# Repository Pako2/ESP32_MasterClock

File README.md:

# ESP32_MasterClock
## Introduction
The project addresses the solution of a simple source of polarized pulses for slave clock networks. The precise time is obtained from the internet using the NTP protocol. The heart of the device is the **ESP32-C3 SuperMini** module, which connects to the internet via WiFi. A prerequisite for the proper functioning of the device is, of course, an available WiFi signal at the deployment location.
The distribution of pulses is managed by a module equipped with two **A4950** H-bridges. The design of the module was chosen primarily to ensure easy repair in case of failure. The advantage of the dual configuration is that in the event of a failure of one bridge, it should be sufficient to rotate the module and thus use the second, previously unused bridge.
The device does not contain any adjustment elements or a display. All settings are done through a web interface. The status of the device is indicated using two LEDs. The first LED is used to indicate the status of WiFi (via a steady light or blinking). The second LED is a multi-colored (WS2812) and indicates the status of the slave clock using different colors.

Complete project documentation can be found in the [UserGuide_EN.pdf](doc/UserGuide_EN.pdf) file.

## Design of the device
The wiring diagram and circuit board were created using the Eagle design system.
### Wiring diagram

### Printed circuit board

### A box
The size of the printed circuit board and the spacing of the mounting holes were adjusted after the design so that the board fits into some - existing on the market - box. A box with dimensions of 83 x 58 x 33 mm fits perfectly.

## Choice of components
Even before the design started, I was clear that one of the ESP32 chips/modules would be used in the device, and it would be one of the many existing modules to ensure easy replacement in case of failure. In the end, I chose one of the smallest modules – **ESP32-C3 SuperMini**. It is small, cheap and more than adequately equipped for the given use.

The device is powered by a voltage of 24V, which is required for the correct operation of the slave clock. However, the ESP32-C3 SuperMini module needs a voltage of 5V and therefore a suitable step-down module is used as a power source.

The selected converter is sufficiently dimensioned both in terms of input voltage (up to 40V) and output current (up to 3A).

One of the most important components of the entire device is the H-bridge, with which polarized pulses are sent to the slave clocks. For this task, I chose the A4950 module equipped with two bridges, but only one of them is used. The second one can (due to the symmetrical design of the module) be considered as a "spare". In case of failure of the first bridge, it is enough to turn the module by 180°.

### Time
The device obtains the exact time from an NTP server. This requires the ESP32 to be connected to the Internet. A possible failure of Internet connectivity only affects the accuracy of the operation, and after the connection is restored, the synchronization with the NTP server (and thus also the accuracy) is automatically restored.
The transition to DST and back is done automatically (thanks to synchronization with the NTP server).
Sometimes it can happen that none of the known WiFi networks are available when the device is turned on (or restarted). Then, of course, it is not possible to synchronize the time with the NTP server. In such an extreme situation, the **Sync Browser Time to Device** button on the **NTP (Time) Settings** page will help.

### License
The code parts written by the author of the **ESP32_MasterClock** project are licensed under [MIT License](LICENSE), 3rd party libraries that are used by this project are licensed under different license schemes, please check them out as well.

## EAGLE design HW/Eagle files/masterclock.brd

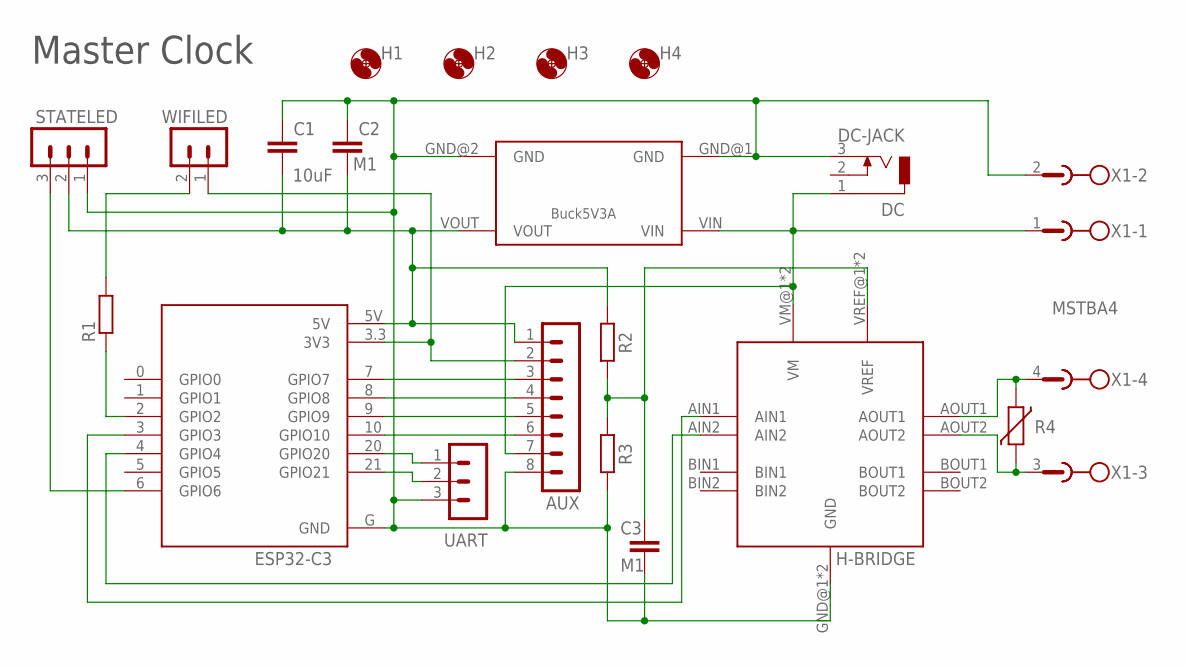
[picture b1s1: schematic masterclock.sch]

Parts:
AUX: CON-LSTB_MA08-108; CON-LSTB-MA08-1-NS08
C1: 10uF; C1206
C2, C3: M1; C0805
DC: DC-JACK; DCJ0202
ESP32-C3: ESP32-C3_SUPERMINI; ESP32-C3_SUPERMINI_MODULE_ESP32-C3_SUPERMINI
H1, H2, H3, H4: MOUNT-HOLE3,0-2,5; 3,0-2,5
H-BRIDGE: A4950_MODULE
R1, R2, R3: R-EU_R0805; R0805
R4: VARISTORS07KS07K385; S07K385
STATELED: CON-LSTB_MA03-108; CON-LSTB_MA03-1-NS08
U$3: BUCK5V3A
UART: CON-LSTB_MA03-108; CON-LSTB_MA03-1-NS08
WIFILED: CON-LSTB_MA02-1NS08; CON-LSTB_MA02-1-NS08
X1: MSTBA4

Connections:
3V3: AUX.2, ESP32-C3.3.3 (3V3), WIFILED.1
5V: AUX.1, C1.2, C2.2, ESP32-C3.5V, R2.2, STATELED.2, U$3.VOUT
GND: AUX.8, C1.1, C2.1, C3.2, DC.3, ESP32-C3.G (GND), H-BRIDGE.GND@1 (GND), H-BRIDGE.GND@2 (GND), R3.1, STATELED.1, U$3.GND@1 (GND), U$3.GND@2 (GND), UART.3, X1.2
GPIO7: AUX.3, ESP32-C3.7 (GPIO7)
GPIO8: AUX.4, ESP32-C3.8 (GPIO8)
GPIO9: AUX.5, ESP32-C3.9 (GPIO9)
GPIO10: AUX.6, ESP32-C3.10 (GPIO10)
unnamed: ESP32-C3.2 (GPIO2), R1.1
unnamed: ESP32-C3.3 (GPIO3), H-BRIDGE.AIN1
unnamed: ESP32-C3.4 (GPIO4), H-BRIDGE.AIN2
unnamed: ESP32-C3.6 (GPIO6), STATELED.3
unnamed: R1.2, WIFILED.2
OUT1: H-BRIDGE.AOUT1, R4.2, X1.4
OUT2: H-BRIDGE.AOUT2, R4.1, X1.3
RX: ESP32-C3.20 (GPIO20), UART.1
TX: ESP32-C3.21 (GPIO21), UART.2
VIN: AUX.7, DC.1, H-BRIDGE.VM@1 (VM), H-BRIDGE.VM@2 (VM), U$3.VIN, X1.1
VREF: C3.1, H-BRIDGE.VREF@1 (VREF), H-BRIDGE.VREF@2 (VREF), R2.1, R3.2

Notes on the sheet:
Master Clock

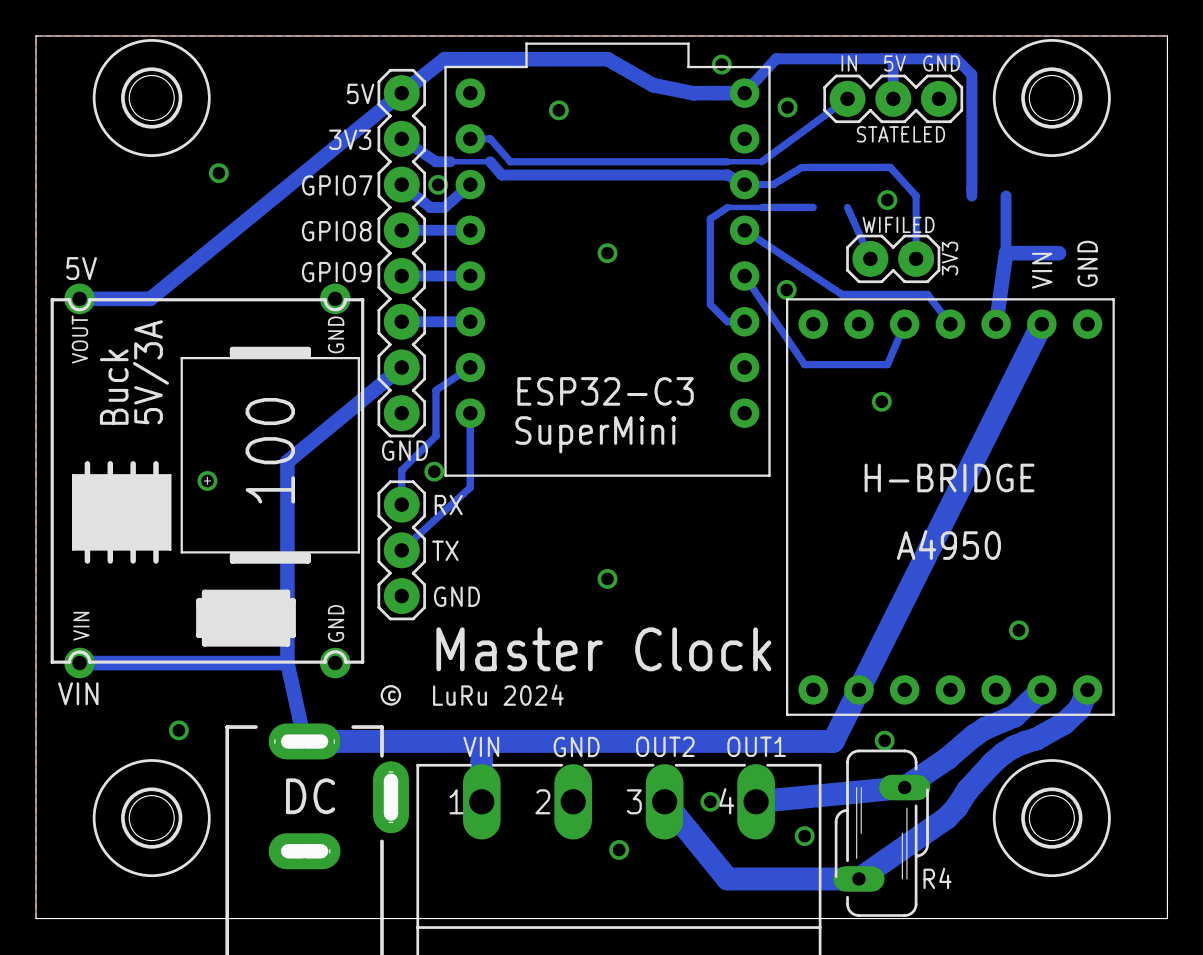
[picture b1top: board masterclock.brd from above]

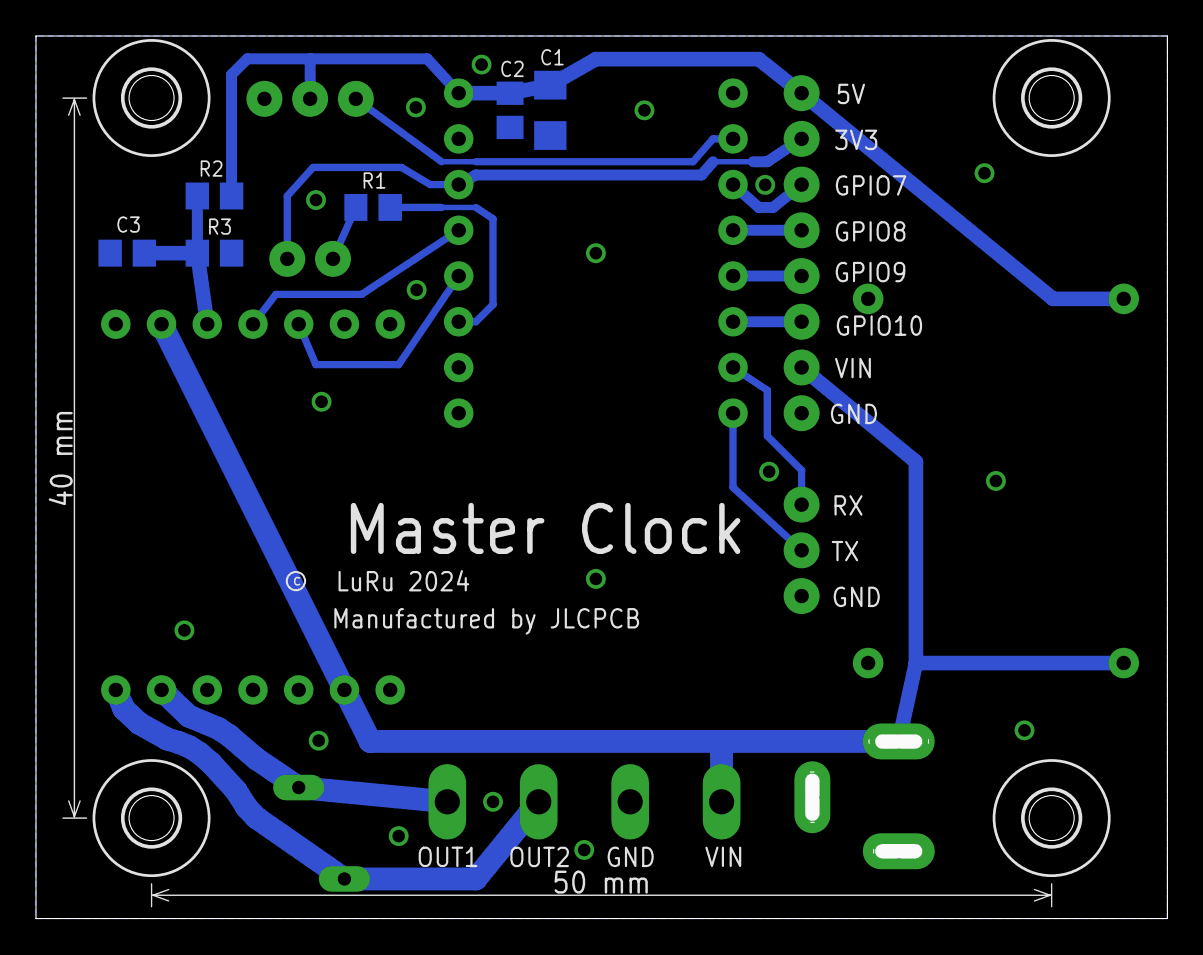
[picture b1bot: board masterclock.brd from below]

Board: 2 copper layers, 62.9 x 49.0 mm, 20 parts (6 on the bottom side), 18 nets.

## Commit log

2024-11-13 initial project version
2024-11-13 README.md update
2024-11-13 ignore __pycache__
2024-11-14 removing old gerber files
